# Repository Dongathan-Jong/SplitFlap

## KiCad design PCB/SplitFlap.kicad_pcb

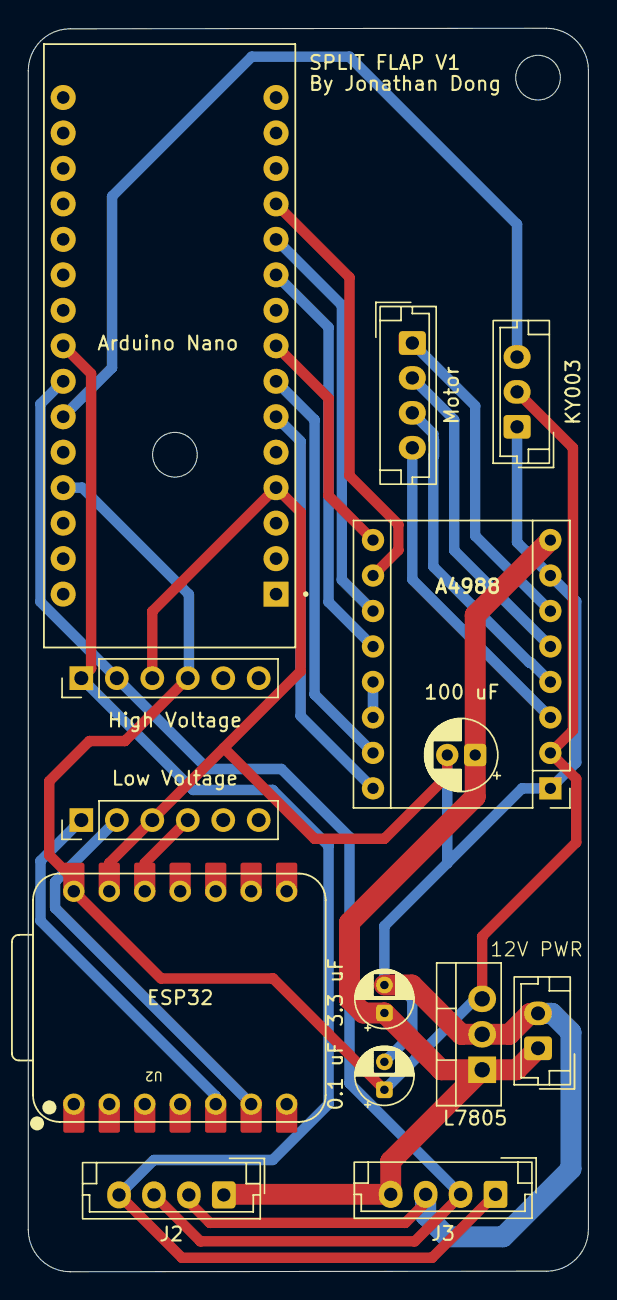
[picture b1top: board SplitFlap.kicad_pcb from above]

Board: 2 copper layers, 40.1 x 89.0 mm, 14 parts (0 on the bottom side), 21 nets.

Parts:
0.1 uF: 0.1 uF; CP_Radial_D4.0mm_P2.00mm
3.3 uF: 0.33uF; CP_Radial_D4.0mm_P2.00mm
100 uF: 100 uF; CP_Radial_D5.0mm_P2.00mm
Arduino Nano: ARDUINO_NANO; MODULE_ARDUINO_NANO
ESP32: A4988; Pololu_Breakout-16_15.2x20.3mm
High Voltage: High Voltage; PinHeader_1x06_P2.54mm_Vertical
J1: 12V PWR; JST_EH_B2B-EH-A_1x02_P2.50mm_Vertical
J2: Data In; JST_EH_B4B-EH-A_1x04_P2.50mm_Vertical
J3: Data Out; JST_EH_B4B-EH-A_1x04_P2.50mm_Vertical
KY003: KY003; JST_EH_B3B-EH-A_1x03_P2.50mm_Vertical
L7805: L7805; TO-220-3_Vertical
Low Voltage: Low Voltage; PinHeader_1x06_P2.54mm_Vertical
Motor: Motor; JST_EH_B4B-EH-A_1x04_P2.50mm_Vertical
U2: XIAO ESP32C3; XIAO-ESP32-C3-DIP

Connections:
+12V: 3.3 uF.1, 100 uF.1, ESP32.8 (VMOT), J1.1, J2.1, J3.4, L7805.1 (IN)
DRIVER DIR: Arduino Nano.7 (D4), ESP32.15 (STEP)
DRIVER EN: Arduino Nano.8 (D5), ESP32.9 (~ENABLE)
DRIVER STEP: Arduino Nano.6 (D3), ESP32.16 (DIR)
ESP 3V3: Low Voltage.4, U2.12 (VCC_3V3)
ESP SCL: Low Voltage.2, U2.6 (D5)
ESP SDA: Low Voltage.1, U2.5 (D4)
MAGNETPIN: Arduino Nano.25 (A6), KY003.3
MS1: Arduino Nano.10 (D7), ESP32.12 (MS3)
MS2: Arduino Nano.11 (D8), ESP32.11 (MS2)
MS3: Arduino Nano.12 (D9), ESP32.10 (MS1)
NANO 5V: 0.1 uF.1, Arduino Nano.27 (+5V), ESP32.2 (VDD), High Voltage.4, KY003.2, L7805.3 (OUT), U2.14 (VUSB)
NANO GND: 0.1 uF.2, 3.3 uF.2, 100 uF.2, Arduino Nano.4 (GND_4), ESP32.1 (GND), ESP32.7 (GND), High Voltage.3, J1.2, J2.2, J3.3, KY003.1, L7805.2 (GND), Low Voltage.3, U2.13 (GND)
NANO SCL: Arduino Nano.24 (A5), High Voltage.2, J2.3, J3.2
NANO SDA: Arduino Nano.23 (A4), High Voltage.1, J2.4, J3.1
unnamed: ESP32.4 (1A), Motor.3
unnamed: ESP32.3 (1B), Motor.4
unnamed: ESP32.5 (2A), Motor.2
unnamed: ESP32.6 (2B), Motor.1
unnamed: ESP32.13 (~RESET), ESP32.14 (~SLEEP)
unnamed: Arduino Nano.3 (RESET), Arduino Nano.28 (RESET)
